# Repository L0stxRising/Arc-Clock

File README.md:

# Arc-Clock

Arc Clock Is a 4 key Custom Iron man ARC reactor Themed Clock made by me (L0stsky)!!! Its my first project with a pcb.

---

## What is this??
Arc Clock is a Custom alarm clock That is based on the Theme of Iron Man. It Uses a PCB, a 3D Printed case and Various Other sensors (battery if you want!)
The clock has 4 Buttons for Various Funcs like setting alarms, changing time, playing games etc!

---
## Materials Used
Buzzer
Esp32 Wroom
2.25" dispay module
DHT11 Sensor
4* Mx cherry switches and keycaps
Mini 360 Buck
3D printed Case

---

## Operating Modes (Cycle with Button 3)
Arc Clock has 3 Modes:

1. **Mode 0: Iron Man Arc Clock HUD**
   - Animated Arc Reactor graphic with rotating spokes.
   - Large digital clock (`HH:MM:SS`).
   - Live DHT11 temperature and humidity.
   - WiFi connection & alarm status.
   - Tap Touch Sensor for Repulsor blast sound.

2. **Mode 1: Telemetry Dashboard**
   - Visual bar for Temperature and Humidity
   - WiFi network status.
   - Touch sensor state, uptime, and available RAM.

3. **Mode 2: "Arc Dodger" Mini-Game**
   - Fly the Iron Man armor dodging incoming missiles and drones.
   - **B1**: Thrust Up
   - **B2**: Dive Down
   - **Touch Sensor**: Fire Repulsor Beam laser
   - **B4**: Reboot suit / restart game on crash

4. **Mode 3: Alarm Protocol & SFX Test**
   - **B1**: Increment Hour
   - **B2**: Increment Minute
   - **B4**: Toggle Alarm ON/OFF
   - **Touch Sensor**: Trigger Repulsor sound effect test

---

## A web Control!!
1. Has auto Connect to wifi (set the creds in the Code) and Auto Updates Time!!
2. Automatically goes to sleep after inactivity (can be changed)
3. Has a website to control it to make it ring or change the Background and more!

---

## AI Usage
1. Used AI to help me with the PCB making as i didn't understand a single thing about them.
2. Used a Lil AI help in the Code

---

## How to use
1. Download the Repo
2. Update the Code with you wifi Credentials
3. Flash to your esp32!

---

## Creator
Made by L0stsky ;D with KiCad

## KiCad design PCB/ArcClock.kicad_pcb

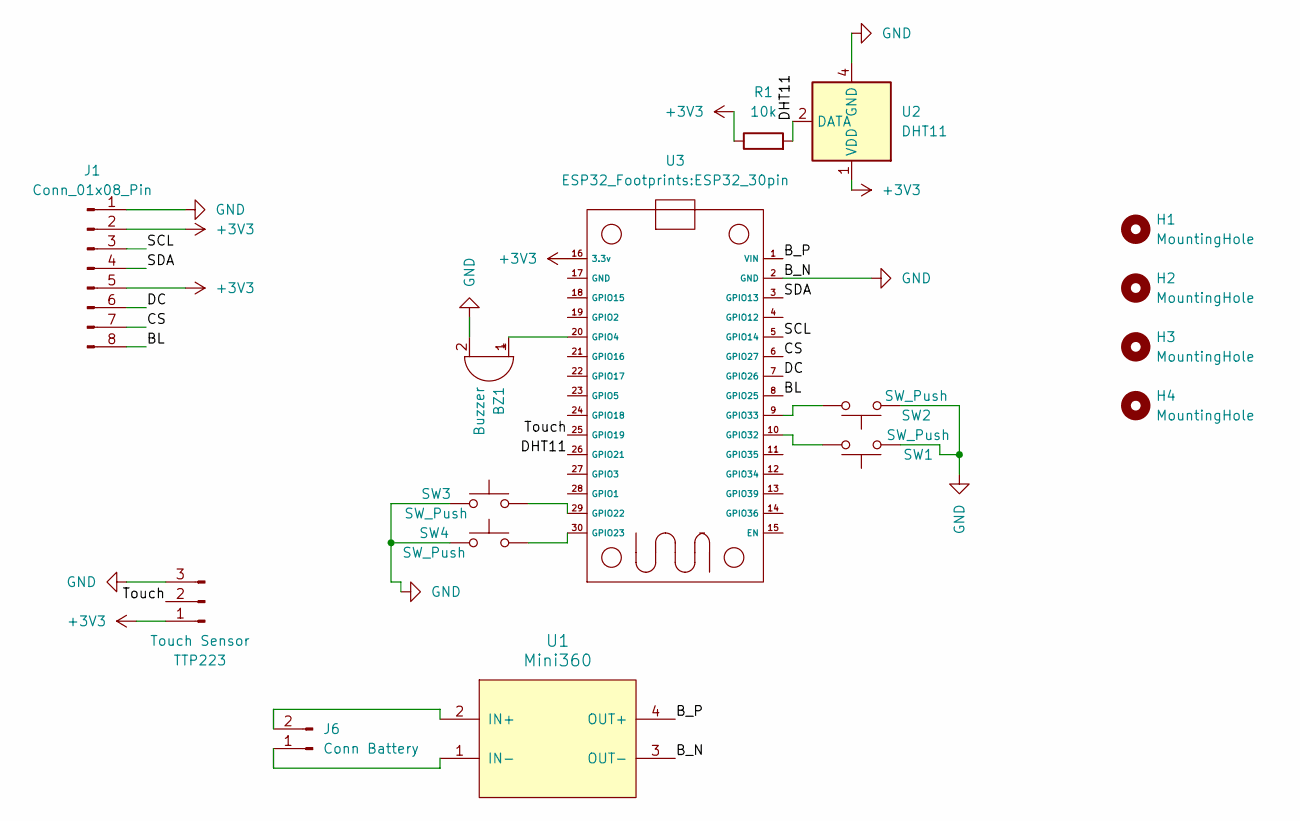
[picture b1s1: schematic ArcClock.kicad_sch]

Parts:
BZ1: Buzzer; Buzzer_12x9.5RM7.6
H1, H2, H3, H4: MountingHole; MountingHole_3.2mm_M3
J1: Conn_01x08_Pin; PinHeader_1x08_P2.54mm_Vertical
J6: Conn Battery; TerminalBlock_Phoenix_MKDS-1,5-2_1x02_P5.00mm_Horizontal
R1: 10k; R_Axial_DIN0207_L6.3mm_D2.5mm_P10.16mm_Horizontal
SW1, SW2, SW3, SW4: SW_Push; SW_Cherry_MX_1.00u_PCB
TTP223: Touch Sensor; TerminalBlock_Phoenix_MKDS-1,5-3_1x03_P5.00mm_Horizontal
U1: Mini360; Mini360_step-down
U2: DHT11; Aosong_DHT11_5.5x12.0_P2.54mm
U3: ESP32_30pin

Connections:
+3V3: J1.2, J1.5, R1.1, TTP223.1, U2.1 (VDD), U3.16 (3.3v)
/BL: J1.8, U3.8 (GPIO25)
/B_P: U1.4 (OUT+), U3.1 (VIN)
/CS: J1.7, U3.6 (GPIO27)
/DC: J1.6, U3.7 (GPIO26)
/DHT11: R1.2, U2.2 (DATA), U3.26 (GPIO21)
/SCL: J1.3, U3.5 (GPIO14)
/SDA: J1.4, U3.3 (GPIO13)
/Touch: TTP223.2, U3.25 (GPIO19)
GND: BZ1.2 (-), J1.1, SW1.1, SW2.1, SW3.1, SW4.1, TTP223.3, U1.3 (OUT-), U2.4 (GND), U3.2 (GND)
unnamed: BZ1.1 (+), U3.20 (GPIO4)
unnamed: J6.1, U1.1 (IN-)
unnamed: J6.2, U1.2 (IN+)
unnamed: SW3.2, U3.29 (GPIO22)
unnamed: SW4.2, U3.30 (GPIO23)
unnamed: SW1.2, U3.10 (GPIO32)
unnamed: SW2.2, U3.9 (GPIO33)

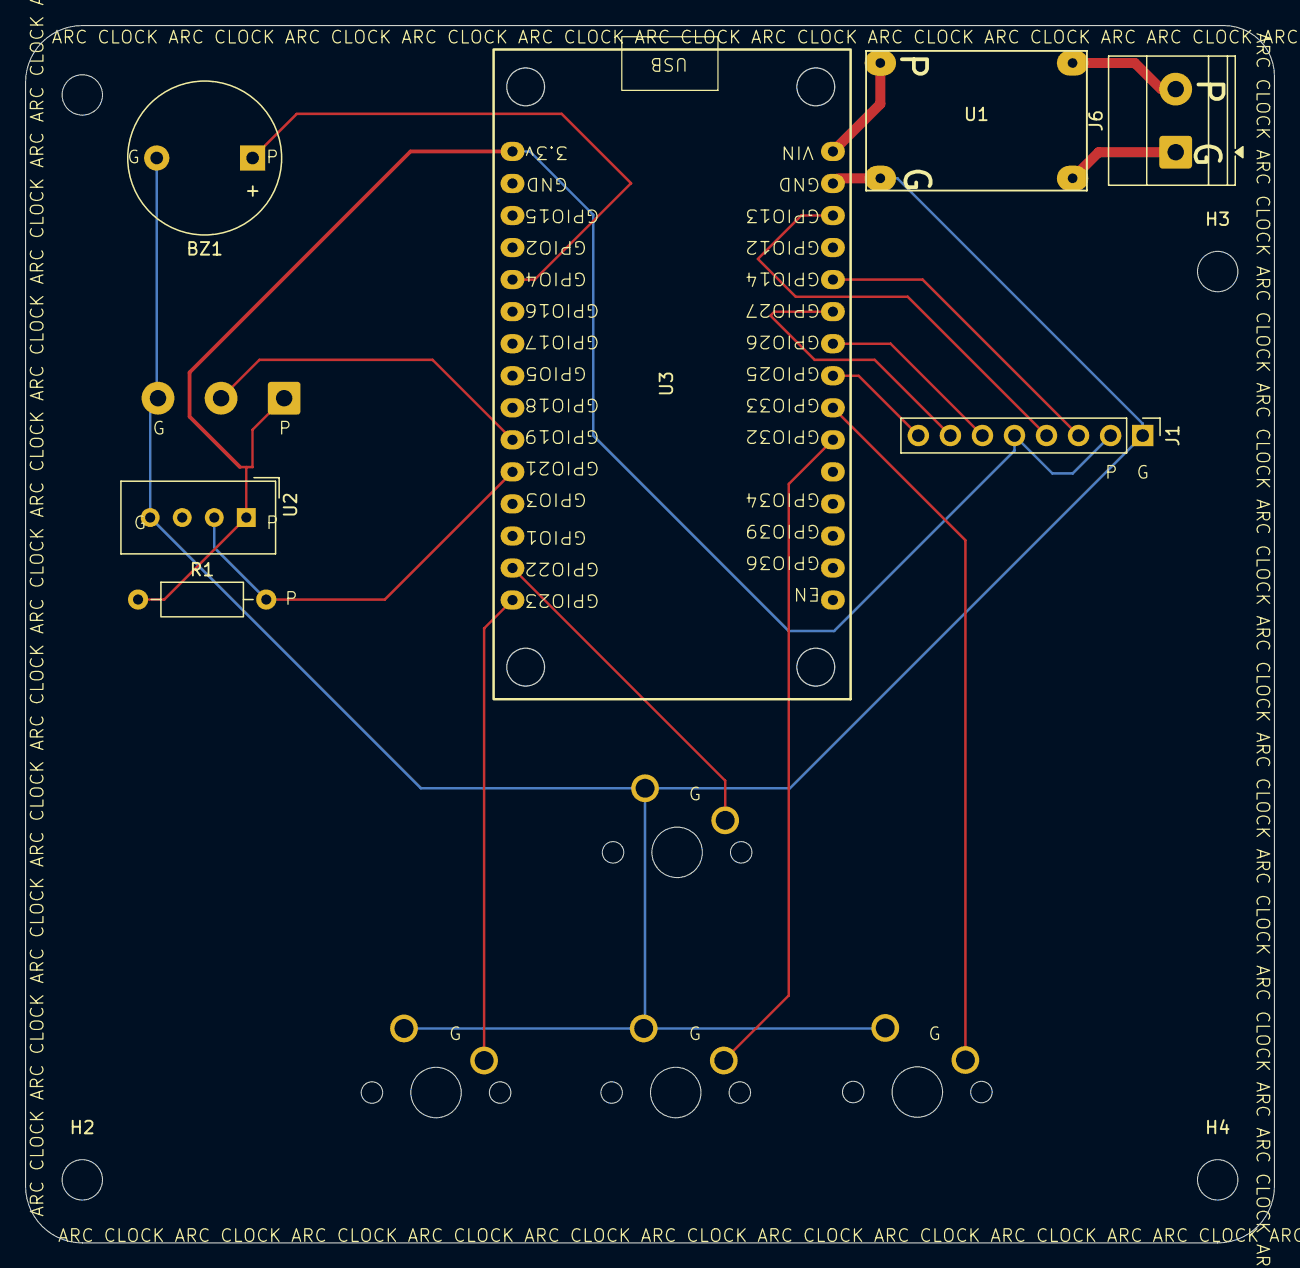
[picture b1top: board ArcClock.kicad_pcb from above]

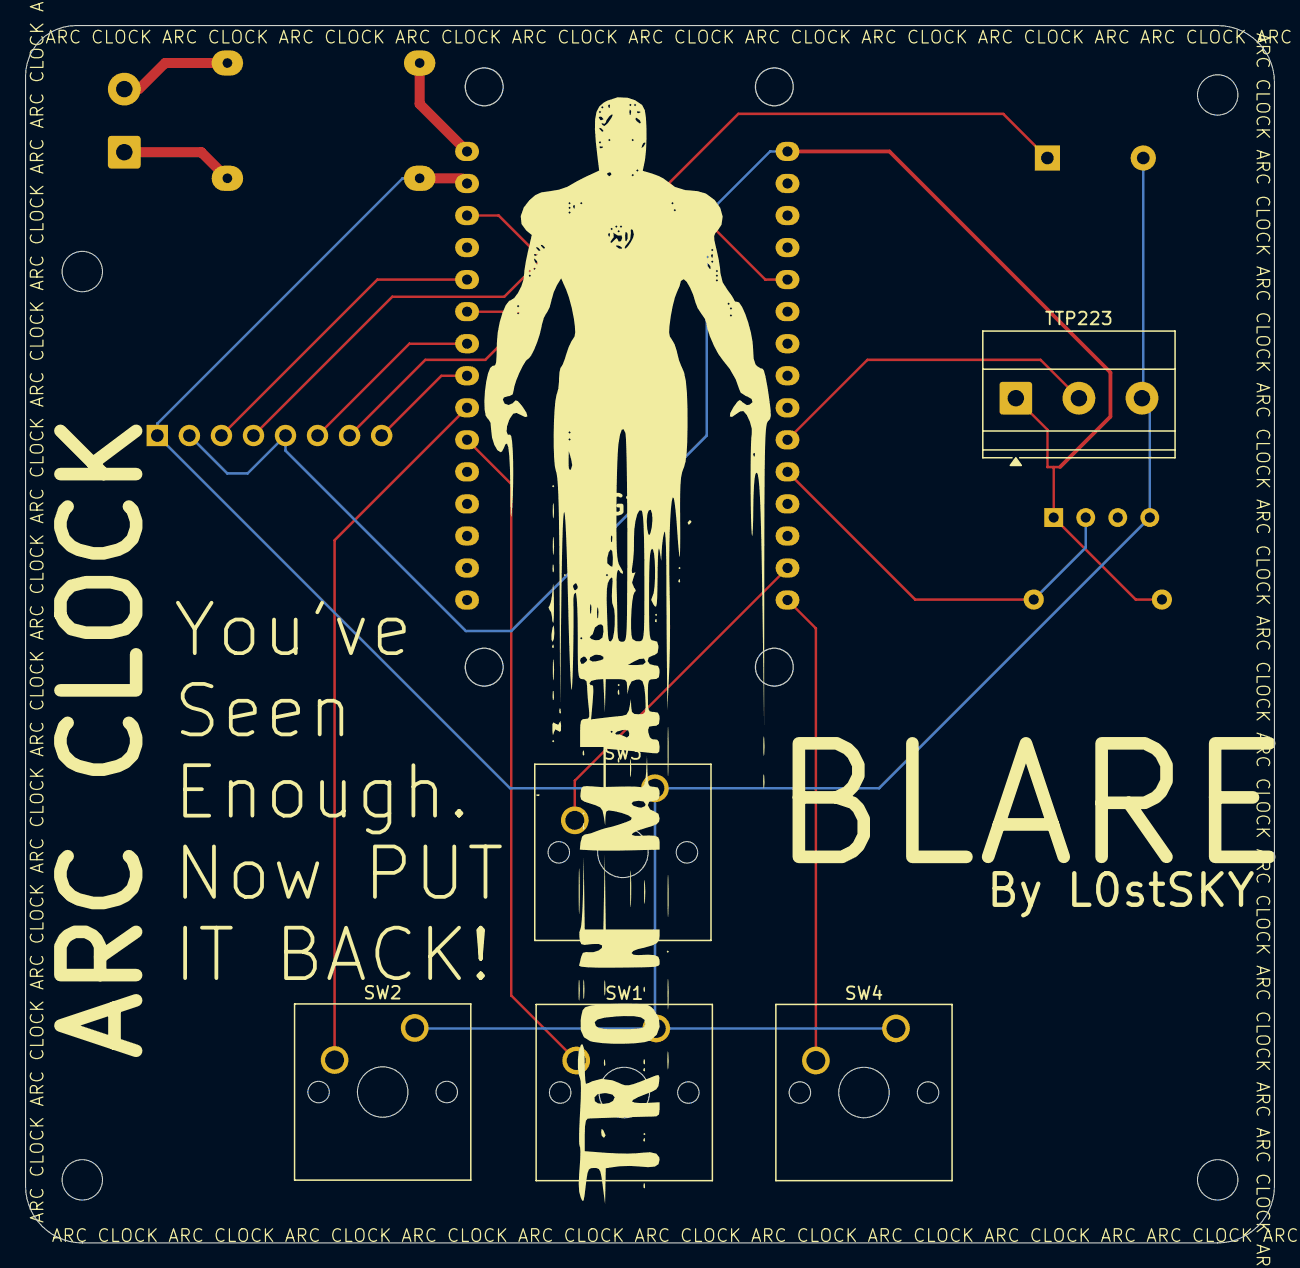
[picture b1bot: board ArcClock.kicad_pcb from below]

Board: 2 copper layers, 99.0 x 96.5 mm, 16 parts (5 on the bottom side), 17 nets.
